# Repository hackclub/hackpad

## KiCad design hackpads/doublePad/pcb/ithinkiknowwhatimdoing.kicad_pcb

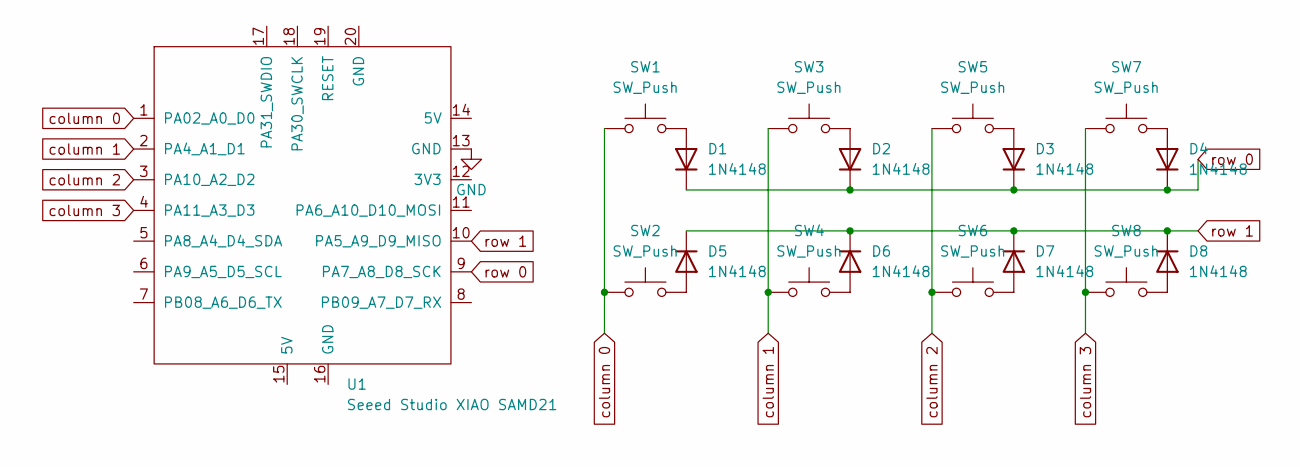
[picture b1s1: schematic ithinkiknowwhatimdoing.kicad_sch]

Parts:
D1, D2, D3, D4, D5, D6, D7, D8: 1N4148; D_DO-35_SOD27_P7.62mm_Horizontal
SW1, SW2, SW3, SW4, SW5, SW6, SW7, SW8: SW_Push; SW_Cherry_MX_1.00u_Plate
U1: Seeed Studio XIAO SAMD21; XIAO-Generic-Thruhole-14P-2.54-21X17.8MM

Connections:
GND: U1.13 (GND)
unnamed: D1.2 (A), SW1.2
unnamed: D2.2 (A), SW3.2
unnamed: D3.2 (A), SW5.2
unnamed: D4.2 (A), SW7.2
unnamed: D5.2 (A), SW2.2
unnamed: D6.2 (A), SW4.2
unnamed: D7.2 (A), SW6.2
unnamed: D8.2 (A), SW8.2
column 0: SW1.1, SW2.1, U1.1 (PA02_A0_D0)
column 1: SW3.1, SW4.1, U1.2 (PA4_A1_D1)
column 2: SW5.1, SW6.1, U1.3 (PA10_A2_D2)
column 3: SW7.1, SW8.1, U1.4 (PA11_A3_D3)
row 0: D1.1 (K), D2.1 (K), D3.1 (K), D4.1 (K), U1.9 (PA7_A8_D8_SCK)
row 1: D5.1 (K), D6.1 (K), D7.1 (K), D8.1 (K), U1.10 (PA5_A9_D9_MISO)

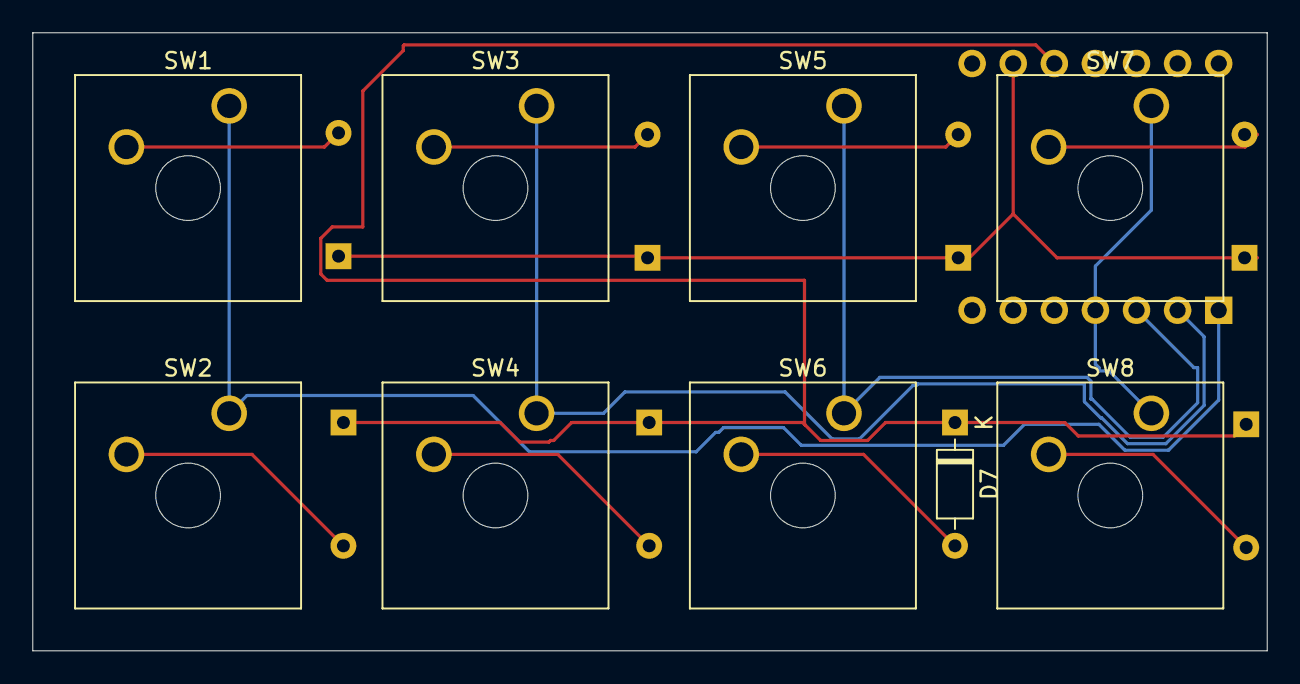
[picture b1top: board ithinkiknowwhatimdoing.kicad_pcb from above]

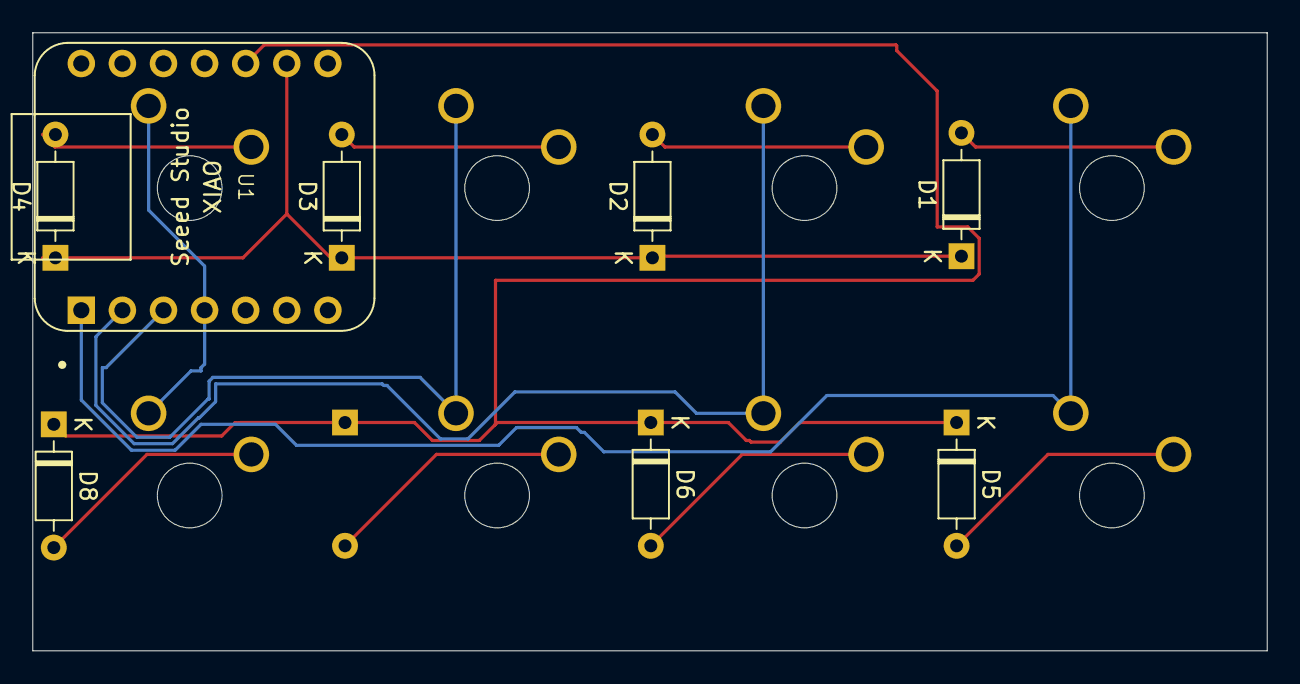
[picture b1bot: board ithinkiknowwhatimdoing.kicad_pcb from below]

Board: 2 copper layers, 76.3 x 38.2 mm, 17 parts (8 on the bottom side), 14 nets.

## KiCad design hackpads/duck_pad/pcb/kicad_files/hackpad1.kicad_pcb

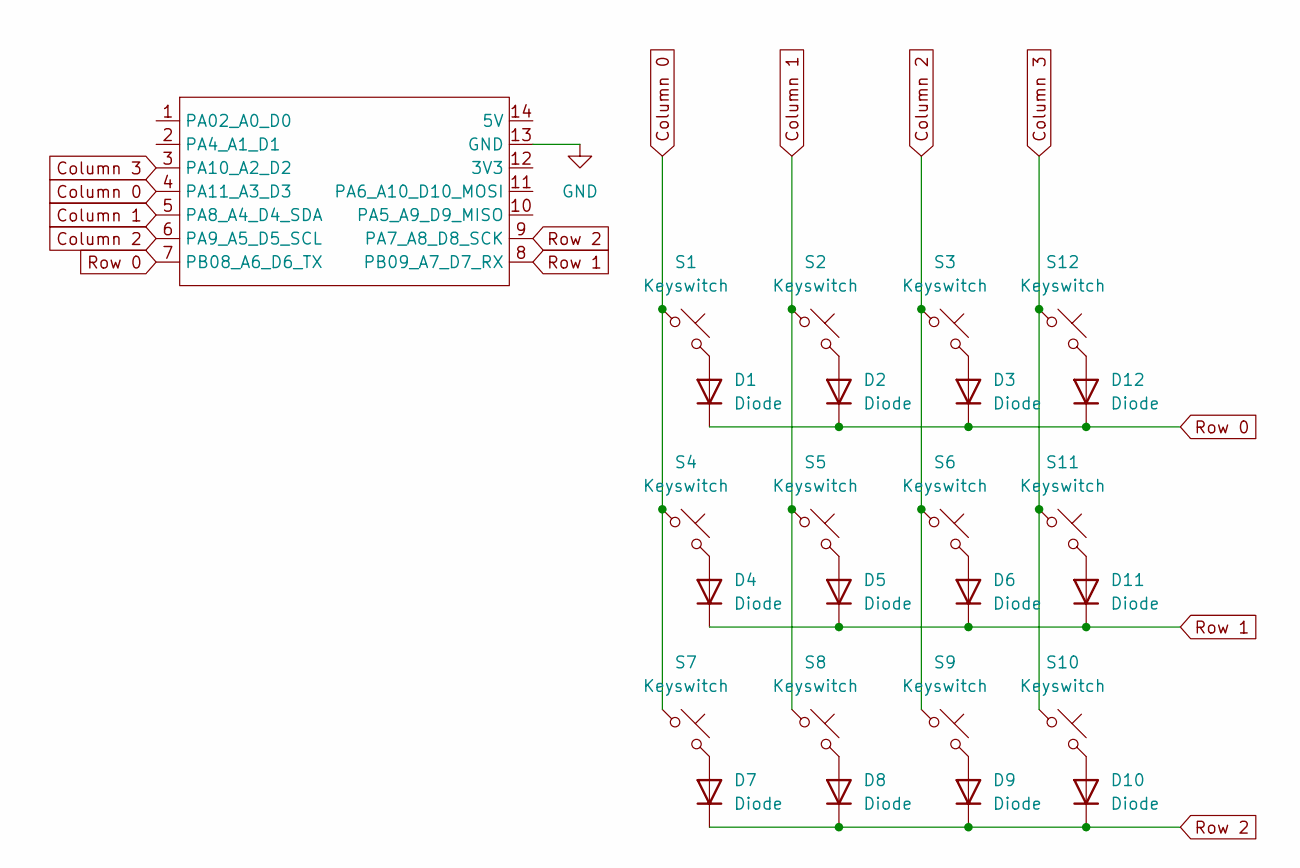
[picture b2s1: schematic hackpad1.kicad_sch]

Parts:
D1, D2, D3, D4, D5, D6, D7, D8, D9, D10, D11, D12: Diode; Diode_DO-35
S1, S2, S3, S4, S5, S6, S7, S8, S9, S10, S11, S12: Keyswitch; MX_PCB_1.00u
U2: MCU_Seeed_XIAO_RP2040; Seeed_XIAO_RP2040

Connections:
Column 0: S1.1, S4.1, S7.1, U2.4 (PA11_A3_D3)
Column 1: S2.1, S5.1, S8.1, U2.5 (PA8_A4_D4_SDA)
Column 2: S3.1, S6.1, S9.1, U2.6 (PA9_A5_D5_SCL)
Column 3: S10.1, S11.1, S12.1, U2.3 (PA10_A2_D2)
GND: U2.13 (GND)
unnamed: D1.2 (A), S1.2
unnamed: D2.2 (A), S2.2
unnamed: D3.2 (A), S3.2
unnamed: D4.2 (A), S4.2
unnamed: D5.2 (A), S5.2
unnamed: D6.2 (A), S6.2
unnamed: D7.2 (A), S7.2
unnamed: D8.2 (A), S8.2
unnamed: D9.2 (A), S9.2
unnamed: D10.2 (A), S10.2
unnamed: D11.2 (A), S11.2
unnamed: D12.2 (A), S12.2
Row 0: D1.1 (K), D2.1 (K), D3.1 (K), D12.1 (K), U2.7 (PB08_A6_D6_TX)
Row 1: D4.1 (K), D5.1 (K), D6.1 (K), D11.1 (K), U2.8 (PB09_A7_D7_RX)
Row 2: D7.1 (K), D8.1 (K), D9.1 (K), D10.1 (K), U2.9 (PA7_A8_D8_SCK)

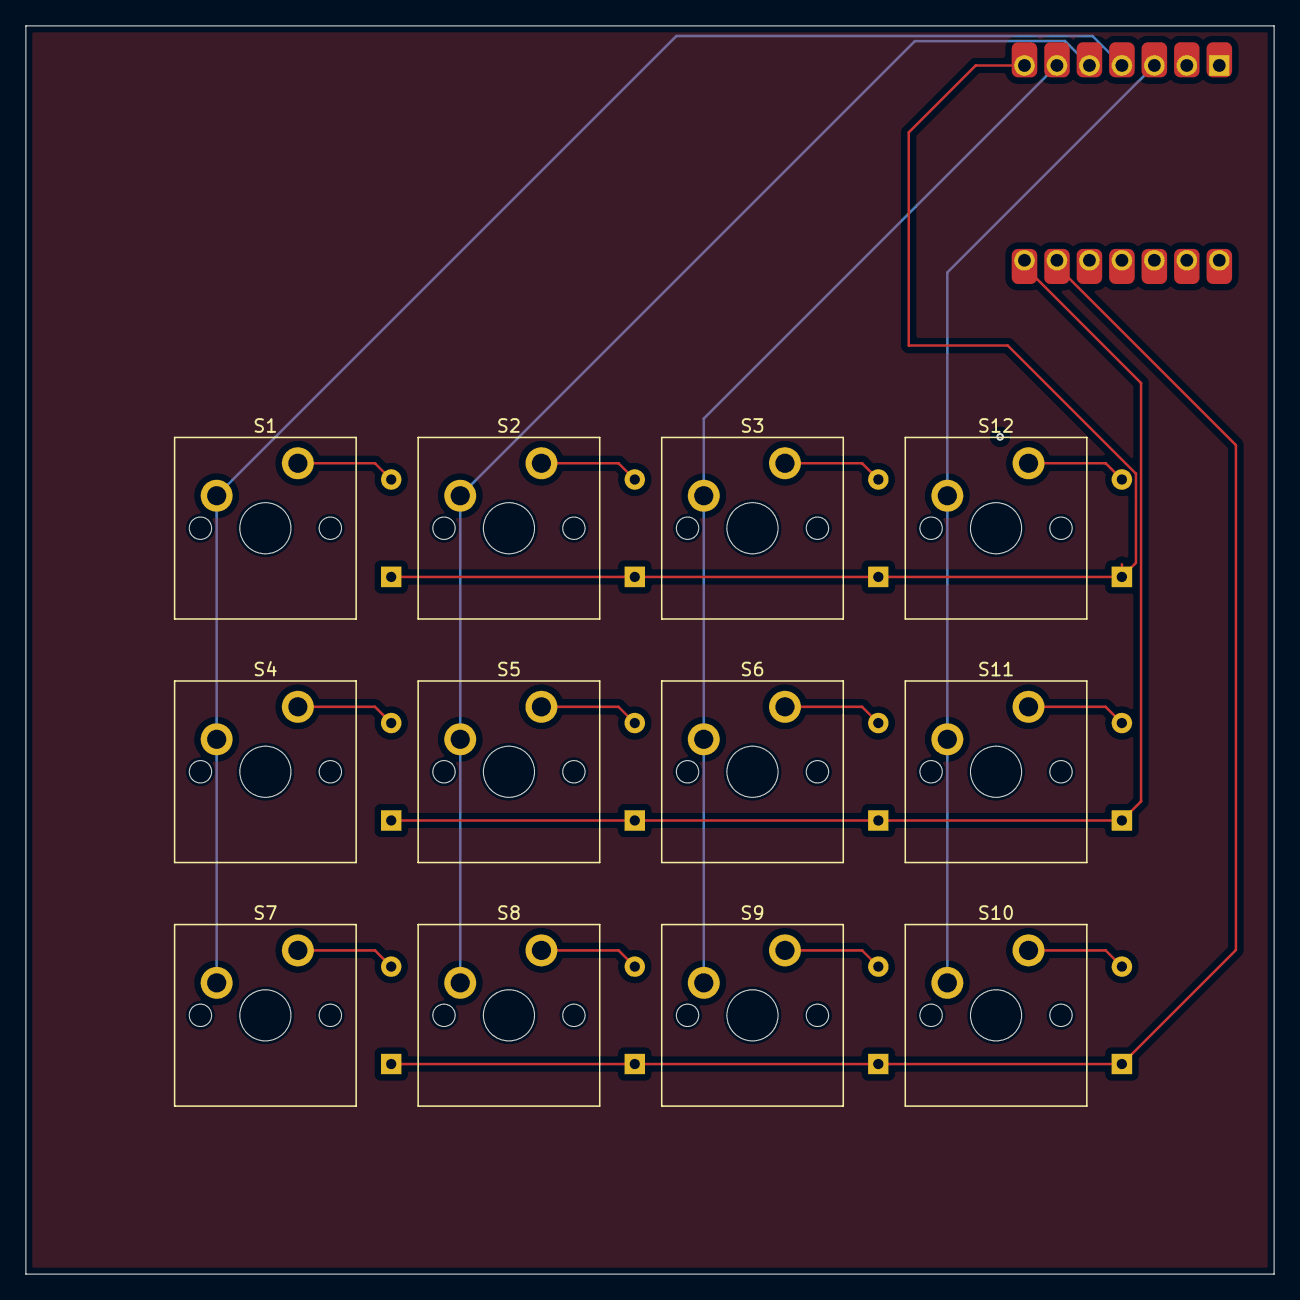
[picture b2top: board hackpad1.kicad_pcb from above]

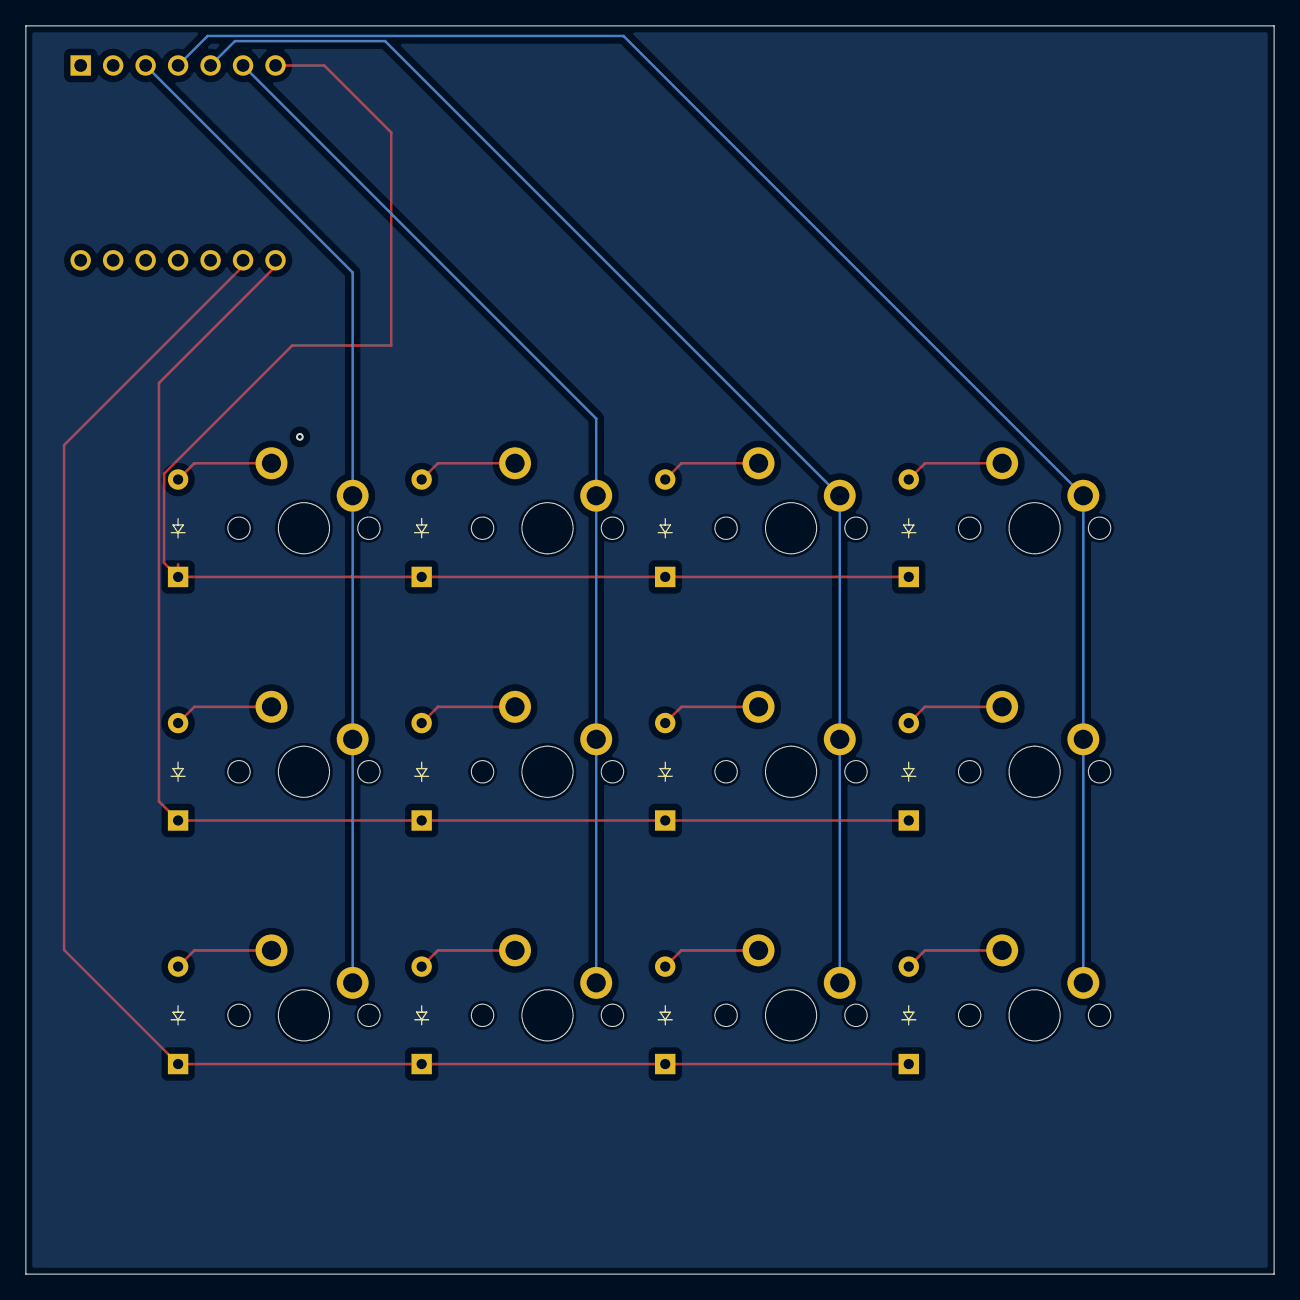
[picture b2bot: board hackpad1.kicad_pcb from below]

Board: 2 copper layers, 97.6 x 97.6 mm, 25 parts (12 on the bottom side), 19 nets.

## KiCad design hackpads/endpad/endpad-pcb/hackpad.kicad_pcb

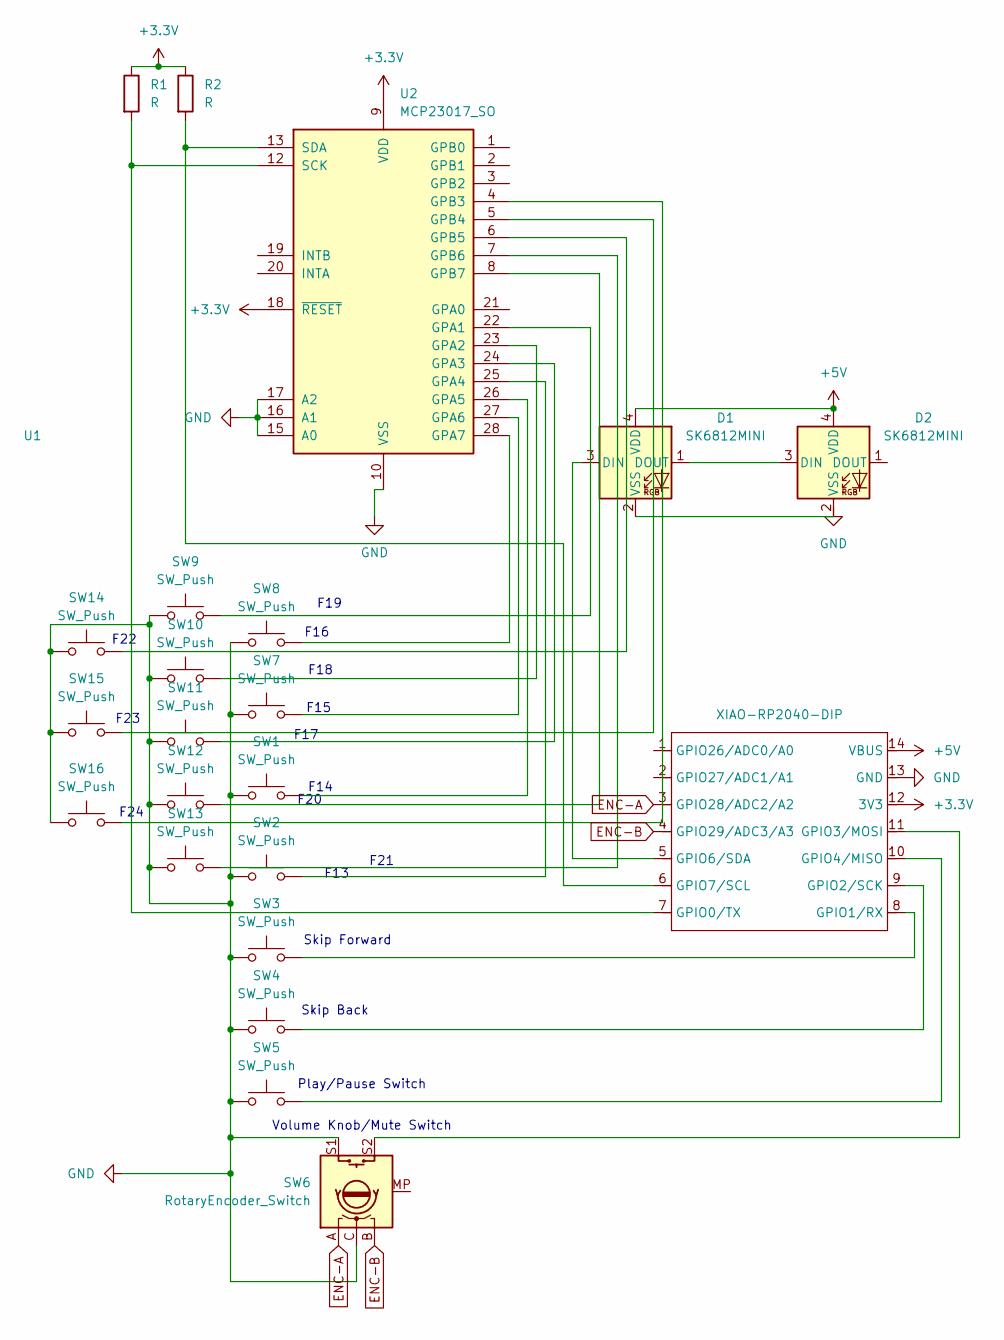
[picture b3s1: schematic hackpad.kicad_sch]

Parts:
D1, D2: SK6812MINI; LED_SK6812MINI_PLCC4_3.5x3.5mm_P1.75mm
R1, R2: R; R_Axial_DIN0204_L3.6mm_D1.6mm_P7.62mm_Horizontal
SW1, SW2, SW3, SW4, SW5, SW7, SW8, SW9, SW10, SW11, SW12, SW13, SW14, SW15, SW16: SW_Push; SW_Cherry_MX_1.00u_PCB
SW6: RotaryEncoder_Switch; RotaryEncoder_Alps_EC11E-Switch_Vertical_H20mm_CircularMoun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
U1: XIAO-RP2040-DIP; XIAO-RP2040-DIP-3D
U2: MCP23017_SO; SOIC-28W_7.5x17.9mm_P1.27mm

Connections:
+3.3V: R1.1, R2.1, U1.12 (3V3), U2.9 (VDD), U2.18 (~RESET)
+5V: D1.4 (VDD), D2.4 (VDD), U1.14 (VBUS)
ENC-A: SW6.A, U1.3 (GPIO28/ADC2/A2)
ENC-B: SW6.B, U1.4 (GPIO29/ADC3/A3)
GND: SW1.1, SW2.1, SW3.1, SW4.1, SW5.1, SW6.C, SW6.S1, SW7.1, SW8.1, SW9.1, SW10.1, SW11.1, SW12.1, SW13.1, SW14.1, SW15.1, SW16.1, U1.13 (GND), U2.10 (VSS), U2.15 (A0), U2.16 (A1), U2.17 (A2)
unnamed: D1.3 (DIN), U1.5 (GPIO6/SDA)
unnamed: D1.1 (DOUT), D2.3 (DIN)
unnamed: D1.2 (VSS), D2.2 (VSS)
unnamed: R1.2, U1.7 (GPIO0/TX), U2.12 (SCK)
unnamed: SW3.2, U1.8 (GPIO1/RX)
unnamed: SW4.2, U1.9 (GPIO2/SCK)
unnamed: SW6.S2, U1.11 (GPIO3/MOSI)
unnamed: SW5.2, U1.10 (GPIO4/MISO)
unnamed: R2.2, U1.6 (GPIO7/SCL), U2.13 (SDA)
unnamed: SW9.2, U2.22 (GPA1)
unnamed: SW10.2, U2.23 (GPA2)
unnamed: SW11.2, U2.24 (GPA3)
unnamed: SW2.2, U2.25 (GPA4)
unnamed: SW1.2, U2.26 (GPA5)
unnamed: SW7.2, U2.27 (GPA6)
unnamed: SW8.2, U2.28 (GPA7)
unnamed: SW16.2, U2.4 (GPB3)
unnamed: SW15.2, U2.5 (GPB4)
unnamed: SW14.2, U2.6 (GPB5)
unnamed: SW13.2, U2.7 (GPB6)
unnamed: SW12.2, U2.8 (GPB7)

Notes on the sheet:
F16
F18
F13
F17
F23
Volume Knob/Mute Switch
F19
Skip Forward
F20
F22
F24
F15
Skip Back
F21
Play/Pause Switch
F14

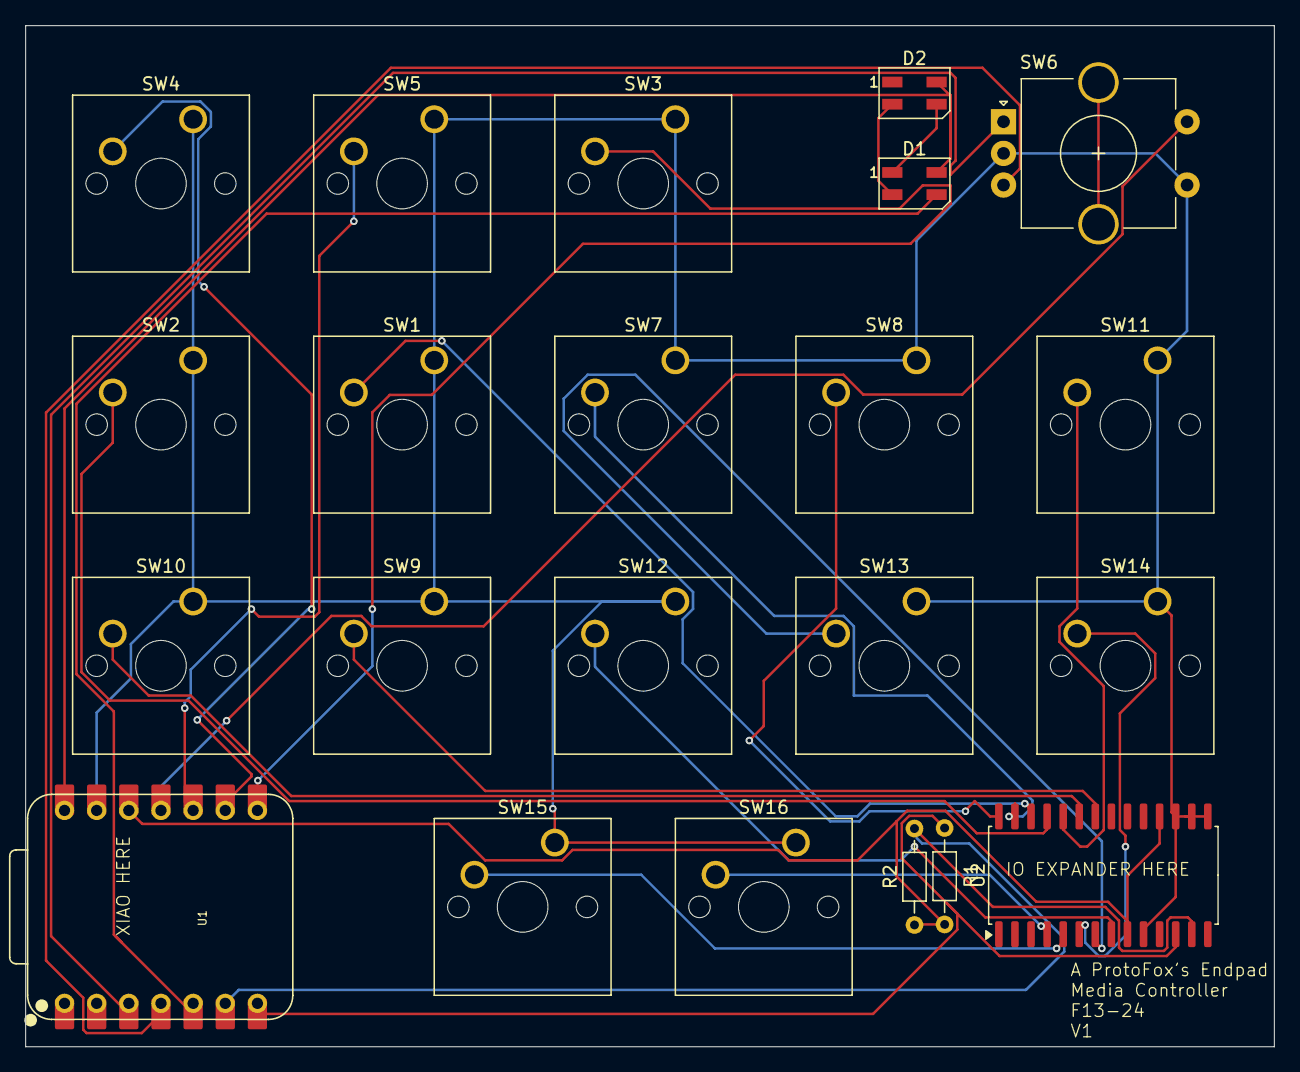
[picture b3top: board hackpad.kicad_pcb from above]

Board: 2 copper layers, 98.7 x 80.7 mm, 22 parts (0 on the bottom side), 26 nets.

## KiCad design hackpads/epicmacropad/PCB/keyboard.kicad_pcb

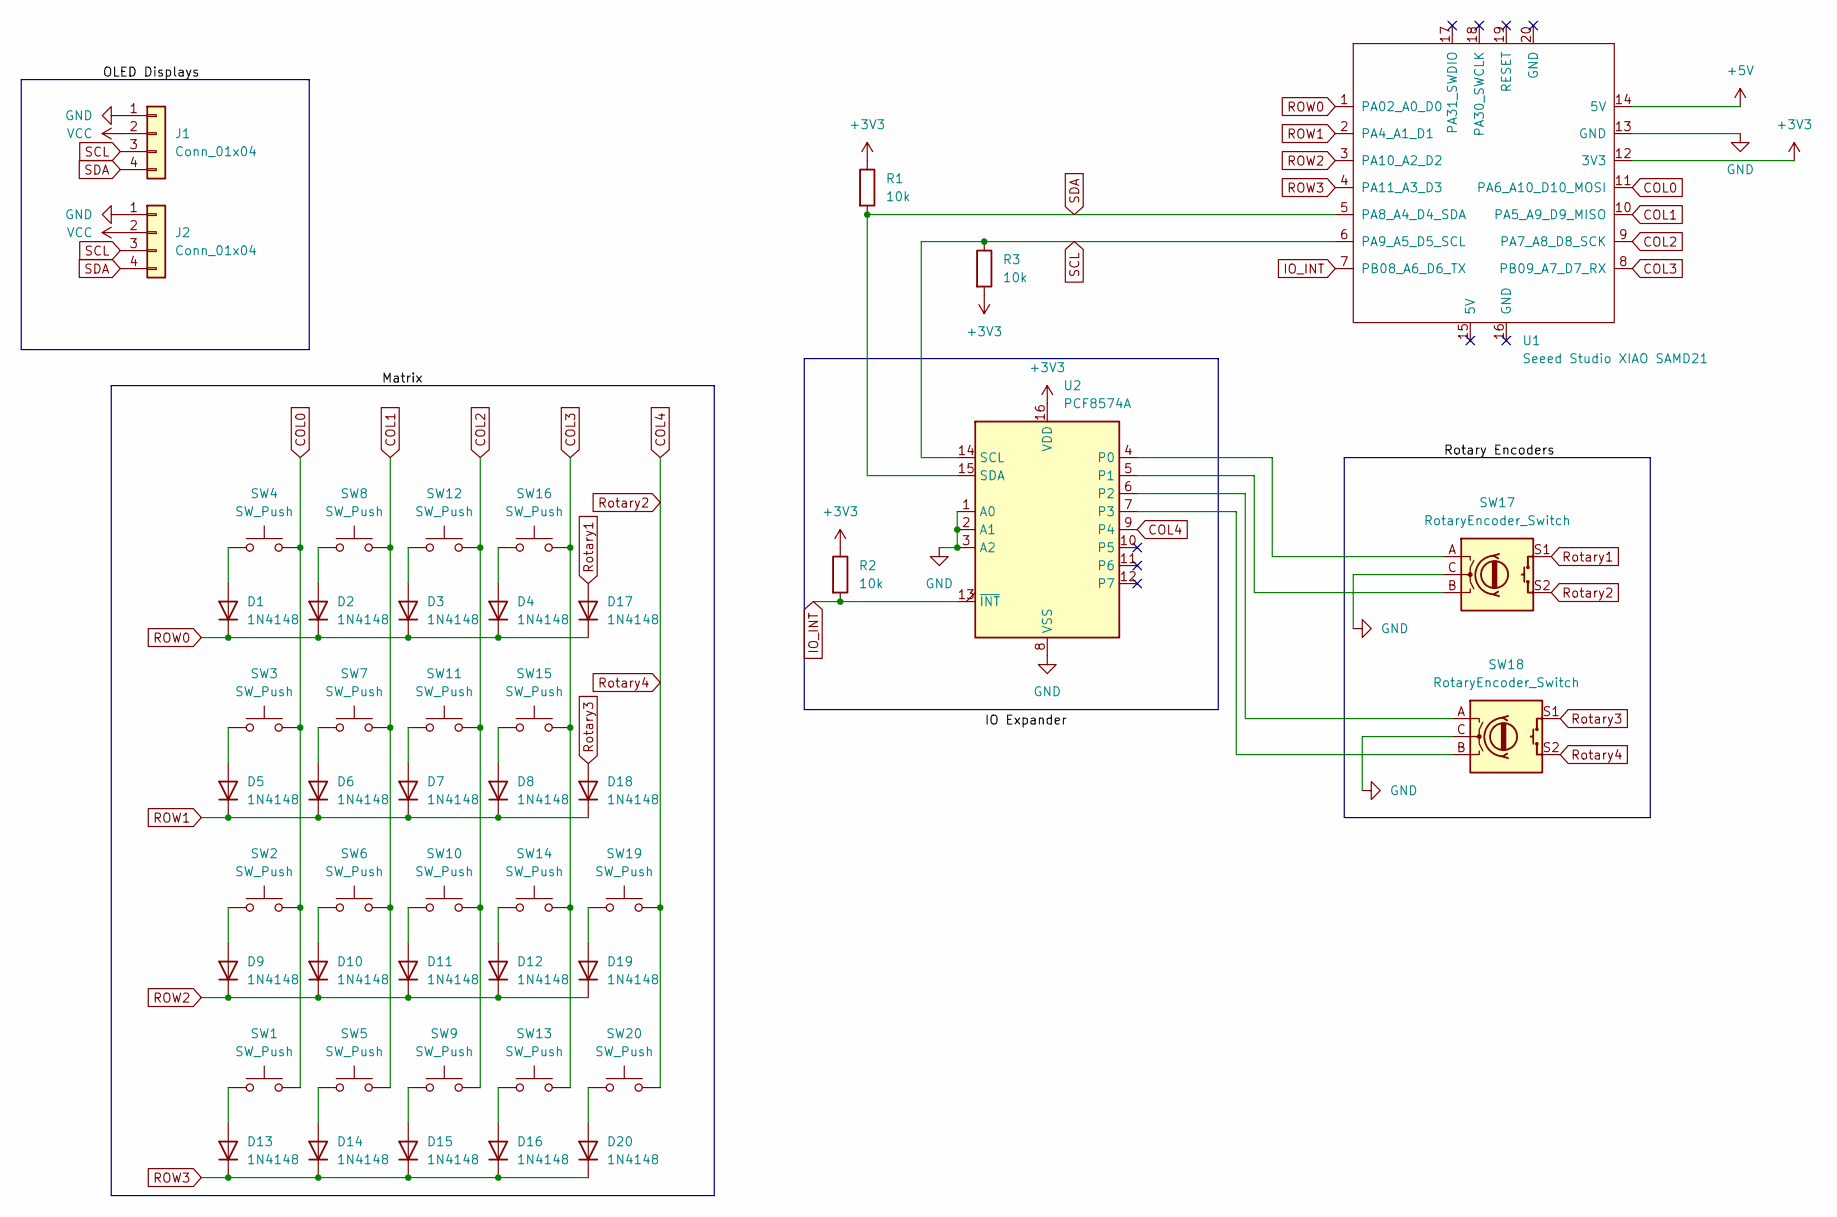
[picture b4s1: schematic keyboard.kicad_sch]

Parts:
D1, D2, D3, D4, D5, D6, D7, D8, D9, D10, D11, D12, D13, D14, D15, D16, D17, D18, D19, D20: 1N4148; D_DO-35_SOD27_P7.62mm_Horizontal
J1, J2: Conn_01x04; SSD1306-0.91-OLED-4pin-128x32
R1, R2, R3: 10k; R_Axial_DIN0204_L3.6mm_D1.6mm_P5.08mm_Horizontal
SW1, SW2, SW3, SW4, SW5, SW6, SW7, SW8, SW9, SW10, SW11, SW12, SW13, SW14, SW15, SW16, SW19, SW20: SW_Push; SW_Cherry_MX_1.00u_PCB
SW17, SW18: RotaryEncoder_Switch; RotaryEncoder_Alps_EC11E-Switch_Vertical_H20mm
U1: Seeed Studio XIAO SAMD21; XIAO-SAMD21-RP2040-14P-2.54-21X17.8MM (Seeeduino XIAO)
U2: PCF8574A

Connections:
+3V3: R1.1, R2.1, R3.2, U1.12 (3V3), U2.16 (VDD)
+5V: U1.14 (5V)
COL0: SW1.2, SW2.2, SW3.2, SW4.2, U1.11 (PA6_A10_D10_MOSI)
COL1: SW5.2, SW6.2, SW7.2, SW8.2, U1.10 (PA5_A9_D9_MISO)
COL2: SW9.2, SW10.2, SW11.2, SW12.2, U1.9 (PA7_A8_D8_SCK)
COL3: SW13.2, SW14.2, SW15.2, SW16.2, U1.8 (PB09_A7_D7_RX)
COL4: SW17.S2, SW18.S2, SW19.2, SW20.2, U2.9 (P4)
GND: J1.1, J2.1, SW17.C, SW18.C, U1.13 (GND), U2.1 (A0), U2.2 (A1), U2.3 (A2), U2.8 (VSS)
IO_INT: R2.2, U1.7 (PB08_A6_D6_TX), U2.13 (~INT)
unnamed: D1.2 (A), SW4.1
unnamed: D2.2 (A), SW8.1
unnamed: D3.2 (A), SW12.1
unnamed: D4.2 (A), SW16.1
unnamed: D5.2 (A), SW3.1
unnamed: D6.2 (A), SW7.1
unnamed: D7.2 (A), SW11.1
unnamed: D8.2 (A), SW15.1
unnamed: D9.2 (A), SW2.1
unnamed: D10.2 (A), SW6.1
unnamed: D11.2 (A), SW10.1
unnamed: D12.2 (A), SW14.1
unnamed: D13.2 (A), SW1.1
unnamed: D14.2 (A), SW5.1
unnamed: D15.2 (A), SW9.1
unnamed: D16.2 (A), SW13.1
unnamed: D19.2 (A), SW19.1
unnamed: D20.2 (A), SW20.1
unnamed: SW17.A, U2.4 (P0)
unnamed: SW17.B, U2.5 (P1)
unnamed: SW18.A, U2.6 (P2)
unnamed: SW18.B, U2.7 (P3)
ROW0: D1.1 (K), D2.1 (K), D3.1 (K), D4.1 (K), D17.1 (K), U1.1 (PA02_A0_D0)
ROW1: D5.1 (K), D6.1 (K), D7.1 (K), D8.1 (K), D18.1 (K), U1.2 (PA4_A1_D1)
ROW2: D9.1 (K), D10.1 (K), D11.1 (K), D12.1 (K), D19.1 (K), U1.3 (PA10_A2_D2)
ROW3: D13.1 (K), D14.1 (K), D15.1 (K), D16.1 (K), D20.1 (K), U1.4 (PA11_A3_D3)
Rotary1: D17.2 (A), SW17.S1
Rotary3: D18.2 (A), SW18.S1
SCL: J1.3, J2.3, R3.1, U1.6 (PA9_A5_D5_SCL), U2.14 (SCL)
SDA: J1.4, J2.4, R1.2, U1.5 (PA8_A4_D4_SDA), U2.15 (SDA)
VCC: J1.2, J2.2

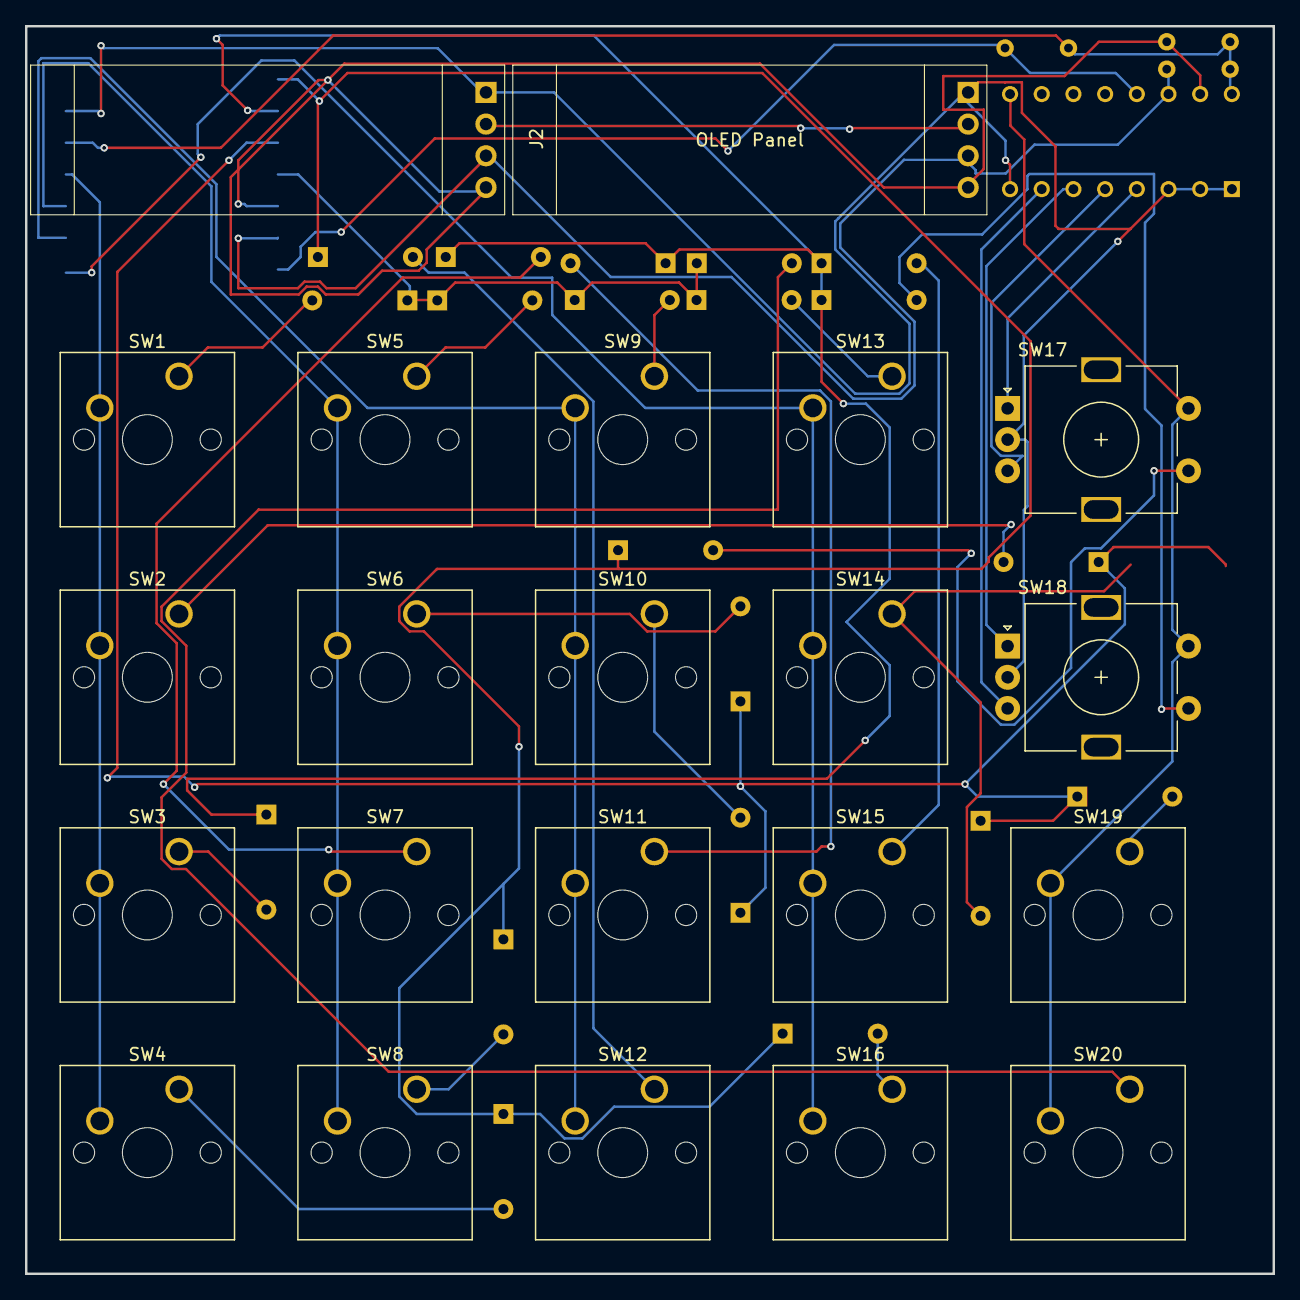
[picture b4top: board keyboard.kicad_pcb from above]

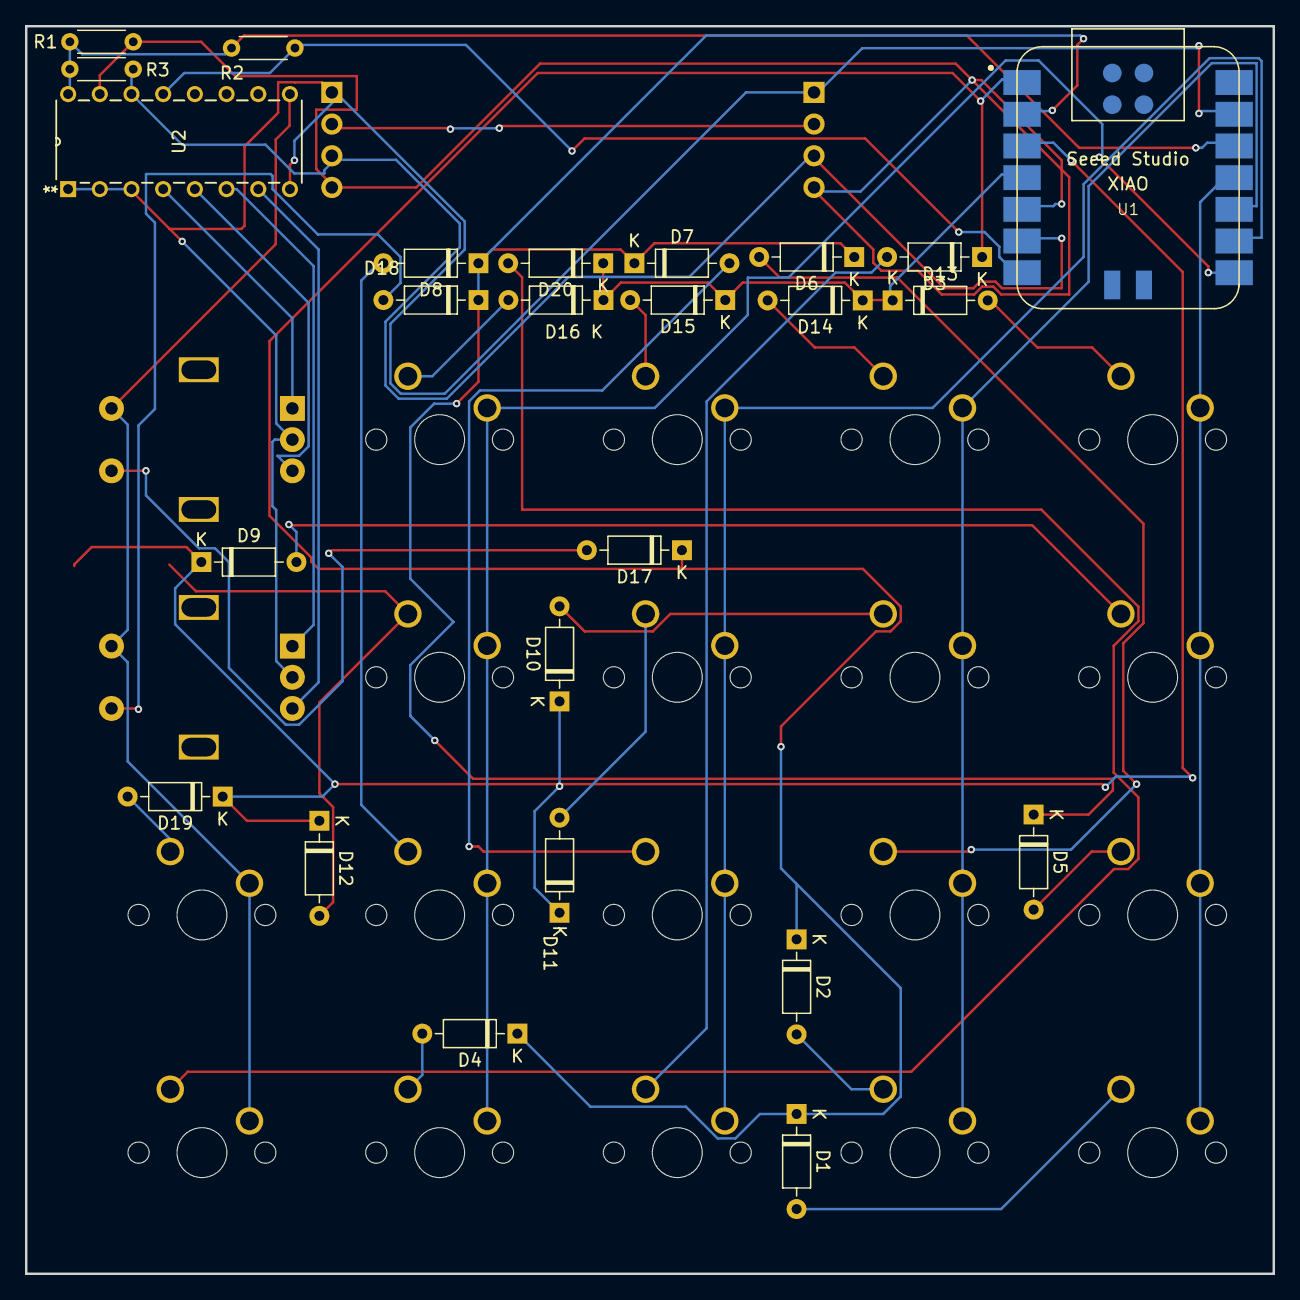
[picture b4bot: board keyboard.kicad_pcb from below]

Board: 2 copper layers, 100.0 x 100.0 mm, 47 parts (25 on the bottom side), 39 nets.

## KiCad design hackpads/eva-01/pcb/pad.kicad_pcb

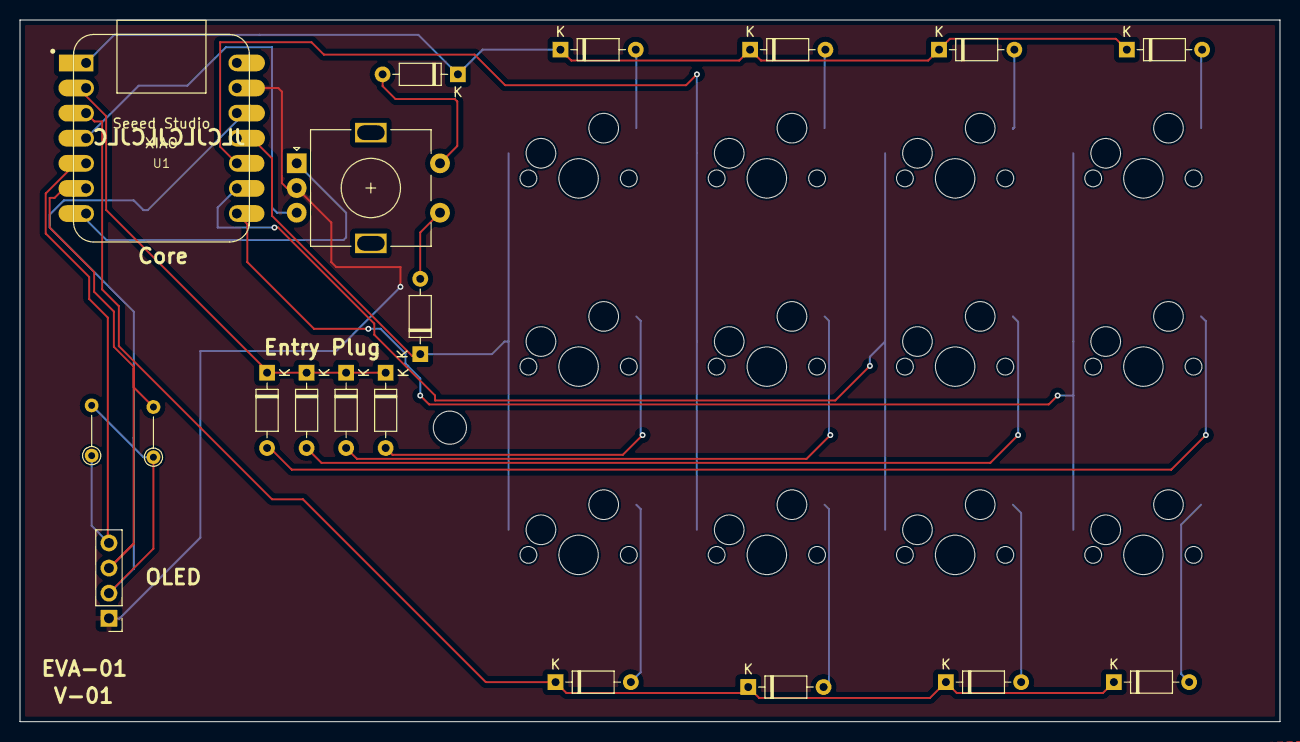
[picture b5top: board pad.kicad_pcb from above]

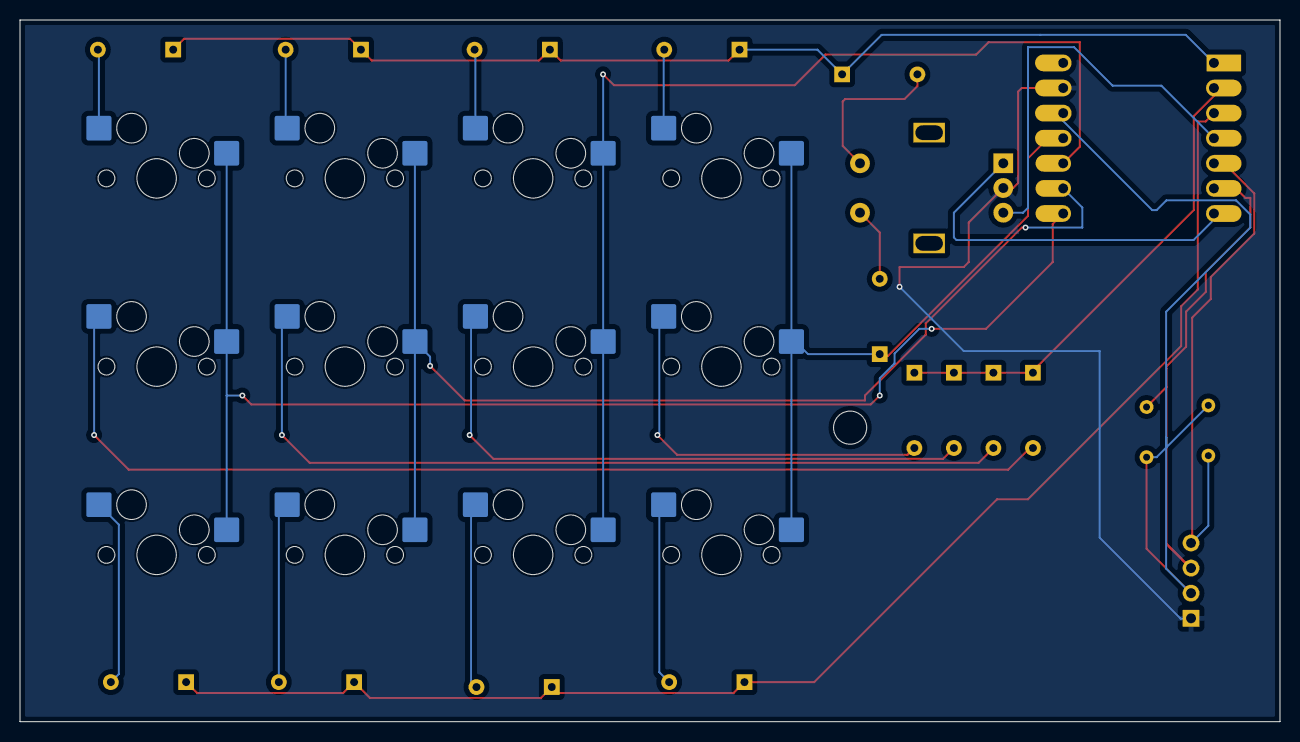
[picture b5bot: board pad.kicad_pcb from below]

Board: 2 copper layers, 127.5 x 71.0 mm, 31 parts (12 on the bottom side), 27 nets.

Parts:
D1, D2, D3, D4, D5, D6, D7, D8, D9, D10, D11, D12, D13, D14: 1N4148; D_DO-35_SOD27_P7.62mm_Horizontal
J1: OLED; PinHeader_1x04_P2.54mm_Vertical
R1, R2: 4.7k; R_Axial_DIN0204_L3.6mm_D1.6mm_P5.08mm_Vertical
SW1, SW2, SW3, SW4, SW6, SW7, SW8, SW9, SW10, SW11, SW12, SW13: SW_Push_45deg; MX-Hotswap-1U
SW5: RotaryEncoder_Switch; RotaryEncoder_Alps_EC11E-Switch_Vertical_H20mm
U1: Seeed Studio XIAO SAMD21; XIAO-Generic-Hybrid-14P-2.54-21X17.8MM

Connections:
Col 0: D14.1 (K), SW1.1, SW6.1, SW10.1, U1.11 (PA6_A10_D10_MOSI)
Col 1: SW2.1, SW7.1, SW11.1, U1.10 (PA5_A9_D9_MISO)
Col 2: SW3.1, SW8.1, SW12.1, U1.9 (PA7_A8_D8_SCK)
Col 3: SW4.1, SW9.1, SW13.1, U1.8 (PB09_A7_D7_RX)
GND: J1.1, SW5.C, U1.13 (GND)
unnamed: D1.2 (A), SW1.2
unnamed: D2.2 (A), SW2.2
unnamed: D3.2 (A), SW3.2
unnamed: D4.2 (A), SW4.2
unnamed: D6.2 (A), SW6.2
unnamed: D7.2 (A), SW7.2
unnamed: D8.2 (A), SW8.2
unnamed: D9.2 (A), SW9.2
unnamed: D10.2 (A), SW10.2
unnamed: D11.2 (A), SW11.2
unnamed: D12.2 (A), SW12.2
unnamed: D13.2 (A), SW13.2
PIN A: SW5.A, U1.7 (PB08_A6_D6_TX)
PIN B: SW5.B, U1.4 (PA11_A3_D3)
ROT B: D14.2 (A), SW5.S1
ROTA: D5.2 (A), SW5.S2
Row 0: D1.1 (K), D2.1 (K), D3.1 (K), D4.1 (K), D5.1 (K), U1.1 (PA02_A0_D0)
Row 1: D6.1 (K), D7.1 (K), D8.1 (K), D9.1 (K), U1.2 (PA4_A1_D1)
Row 2: D10.1 (K), D11.1 (K), D12.1 (K), D13.1 (K), U1.3 (PA10_A2_D2)
SCL: J1.3, R2.2, U1.6 (PA9_A5_D5_SCL)
SDA: J1.4, R1.1, U1.5 (PA8_A4_D4_SDA)
VCC: J1.2, R1.2, R2.1, U1.12 (3V3)
